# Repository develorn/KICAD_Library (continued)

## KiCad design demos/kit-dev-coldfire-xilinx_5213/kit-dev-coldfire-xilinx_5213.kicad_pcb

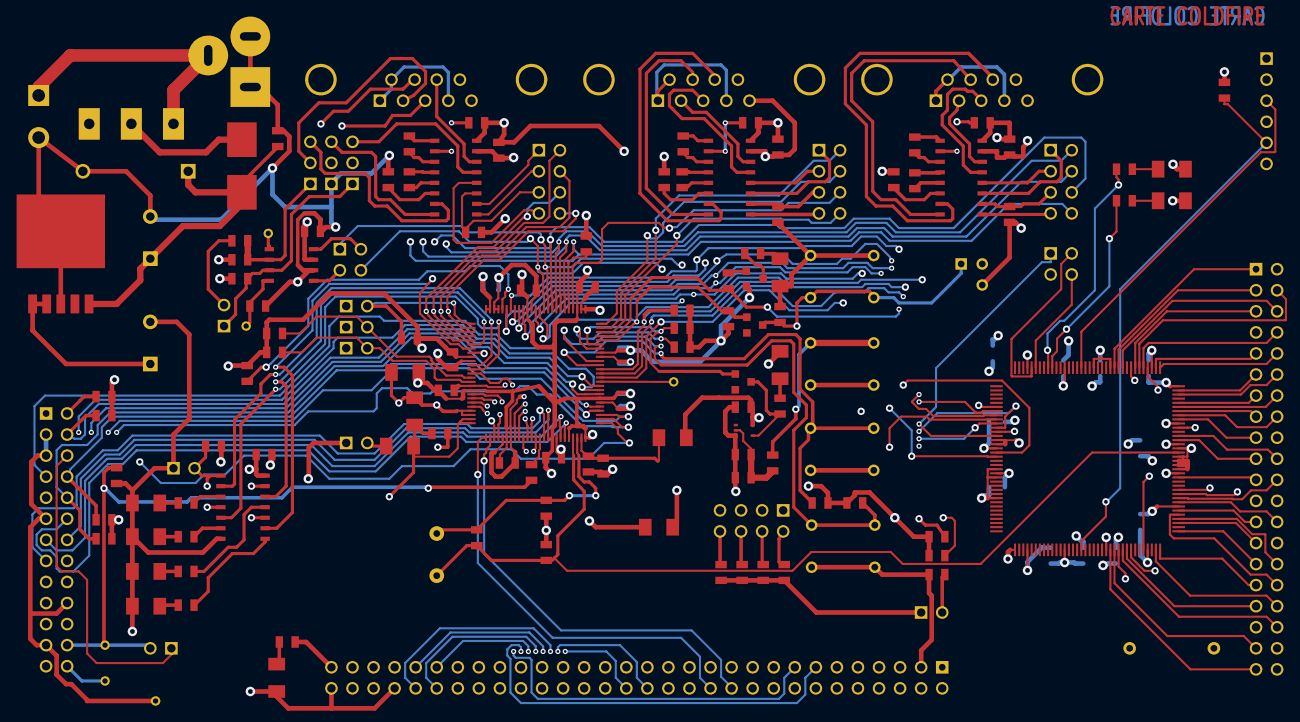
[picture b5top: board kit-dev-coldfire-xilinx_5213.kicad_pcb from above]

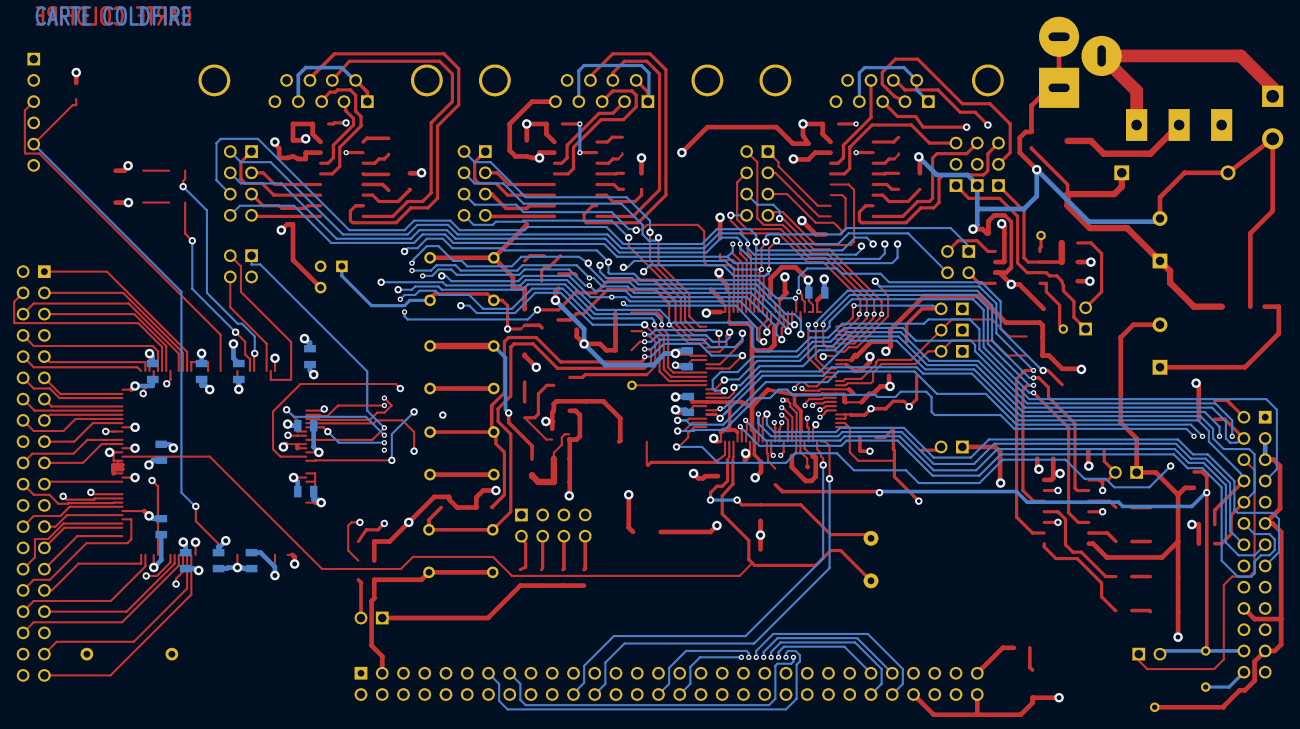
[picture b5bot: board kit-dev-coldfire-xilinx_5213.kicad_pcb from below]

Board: 4 copper layers, 162 parts (14 on the bottom side), 209 nets.

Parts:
ABRT_SW1: SW_PUSH; SW_PUSH_SMALL
ALLPST1: CONN_1; PINTST
BDM_EN1: JUMPER; PIN_ARRAY_2X1
BDM_PORT1: CONN_13X2; pin_array_13x2
C1, C2: 10pF; SM0805
C3, C20: 1nF; SM0805
C4, C5, C6, C7, C8, C9, C10, C11, C12, C14, C15, C18, C21, C22, C23, C24, C25, C26, C27, C28, C30, C31, C32, C33, C34, C35, C36, C41, C43, C44, C45, C46, C51, C52, C53, C54, C55, C56, C57, C58, C59, C60, C61: 100nF; SM0805
C16: 10uF; SM1206POL
C17: 100uF; SM1206POL
C38: 10uF; C2V8
C40: 220uF; C2V8
CAN_EN1: CONN_2X2; PIN_ARRAY_2X2
CAN_TERM1: JUMPER; PIN_ARRAY_2X1
CLK0, CLK1: JUMPER; PIN_ARRAY_2X1
CLKOUT1: CONN_1; PINTST
COM_SEL1, COM_SEL2, COM_SEL3: CONN_3; PIN_ARRAY_3X1
CT1: JUMPER; PIN_ARRAY_2X1
D1, D3: BAT54; ST23AK#1
D7: 1N4004; D5
D8, D9: LED; SM1206POL
F1: FUSE; FSUPCMS
FB1: BEAD; SM1206
GND1: CONN_1; PINTST
J1: JACK_2P; JACK_ALIM
L1, L2: 10uH; SM1206
LED1, LED2, LED3, LED4, LED5: LED; SM1206POL
LEDABRT1: RED; SM1206POL
LED_EN1: JUMPER; PIN_ARRAY_2X1
LV1: DS1818; TO92-INVERT
MCU_PORT1: CONN_30X2; PIN_ARRAY_30X2
P1: CONN_6; PIN_ARRAY-6X1
P3: CONN_2X2; PIN_ARRAY_2X2
P4: CONN_20X2; PIN_ARRAY_20X2
PULUPEN1: CONN_4X2; pin_array_4x2
Q1: 3906; SOT23EBC
R1: 1M; SM0805
R2, R15, R16, R17, R18, R19, R20, R21, R25, R45, R47, R48, R49, R50: 4,7K; SM0805
R4, R5, R6, R8, R10, R11, R13, R23, R26, R30, R34, R35: 10K; SM0805
R7, R36, R62, R63: 1K; SM0805
R9: 0; SM0805
R12: 20K; SM0805
R14, R22, R28, R31, R32, R33, R53: 270; SM0805
R38: 62; SM0805
R46: 22; SM0805
R57: 4K7; SM0805
R64: 3,3; R4
RCAN1, RCAN2: R; SM0805
RED1: LED_RESET1; SM1206POL
RS1: CONN_1; PINTST
RST_SW1: SW_PUSH; SW_PUSH_SMALL
SW1, SW2: SW_PUSH; SW_PUSH_SMALL
SW_ONOFF1: SWITCH_INV; SW_SPDT
TA-1: CONN_1; PINTST
TB1: CONN_2; bornier2
U1: MCF5213-LQFP100; VQFP100
U2: 74AHC1G14; SOT353
U3, U5, U8: MAX202; SO16E
U4: 74HC125; SO14E
U7: PCA82C251; SO8E
U9: XCR3256-TQ144; TQFP144
UARTCAN0, UARTCAN1, UARTCAN2: DB9; DB9FC
UART_EN0, UART_EN1, UART_EN2: CONN_4X2; pin_array_4x2
VDDA1: JUMPER; PIN_ARRAY_2X1
VR1: LT1129_QPACK; DPAK5
VREF1: CONN_1; PINTST
VX_EN1: JUMPER; PIN_ARRAY_2X1
Y1: 8MHz; HC-18UH

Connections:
+3.3V: ABRT_SW1.2, BDM_PORT1.9, BDM_PORT1.25, C4.1, C5.1, C6.1, C7.1, C8.1, C9.1, C10.1, C11.1, C12.1, C14.2, C17.1, C22.1, C23.1, C26.1, C28.1, C30.1, C34.1, C35.1, C40.1, C46.1, C51.1, C52.1, C53.1, C54.1, C55.1, C56.1, C57.1, C58.1, C59.1, C60.1, C61.1, L2.1, LEDABRT1.1, LV1.2, MCU_PORT1.59, P1.1, Q1.1, R2.1, R4.2, R5.2, R6.2, R8.2, R10.2, R11.2, R13.2, R15.1, R16.1, R17.1, R18.1, R19.1, R20.1, R25.1, R34.1, R45.2, R47.1, R48.1, R49.1, R50.1, R53.2, R57.1, R64.1, RCAN1.1, U1.1, U1.2, U1.14, U1.22, U1.23, U1.34, U1.41, U1.55, U1.57, U1.68, U1.81, U1.93, U2.5, U3.16, U4.14, U5.16, U7.3, U8.16, U9.24, U9.50, U9.51, U9.58, U9.73, U9.76, U9.95, U9.115, U9.123, U9.130, U9.144, VDDA1.1, VR1.1, VR1.2, VX_EN1.1
/ALLPST: ALLPST1.1, U1.86
/AN2: MCU_PORT1.14, U1.45
/AN3: MCU_PORT1.16, U1.46
/AN4: MCU_PORT1.18, U1.54
/AN6: MCU_PORT1.22, U1.52
/BKPT-: BDM_PORT1.2, R17.2, U1.76
/CANTX: CAN_EN1.1, MCU_PORT1.26, PULUPEN1.5, U1.10
/CLKIN/EXTAL: C1.1, R1.2, U1.73, Y1.1
/CLKMOD0: CLK0.2, R25.2, U1.40
/CLKMOD1: CLK1.2, R2.2, U1.39
/DDAT0: BDM_PORT1.19, U1.77
/DDAT1: BDM_PORT1.18, U1.78
/DDAT2: BDM_PORT1.17, U1.83
/DDAT3: BDM_PORT1.16, U1.84
/DSCLK: BDM_PORT1.4, R18.2, U1.85
/DSI: BDM_PORT1.8, R19.2, U1.79
/DSO: BDM_PORT1.10, R20.2, U1.80
/DSPI_DOUT: MCU_PORT1.17, U1.17, U9.47
/DTIN1: MCU_PORT1.36, U1.37, U4.5
/GPT1: MCU_PORT1.50, U1.59
/GPT3: MCU_PORT1.52, U1.62
/IRQ-5: MCU_PORT1.35, R10.1, SW2.1, U1.91
/IRQ-6: MCU_PORT1.37, R11.1, U1.94
/IRQ-7: D1.1, MCU_PORT1.39, R13.1, U1.95
/JTAG_EN: BDM_EN1.2, R16.2, U1.26
/PST0: BDM_PORT1.15, U1.65
/PST1: BDM_PORT1.14, U1.66
/PST2: BDM_PORT1.13, U1.69
/PST3: BDM_PORT1.12, U1.70
/PWM1: MCU_PORT1.13, U1.38
/PWM3: MCU_PORT1.15, U1.33
/QSPI_CS3: MCU_PORT1.29, U1.12
/QSPI_DIN: MCU_PORT1.19, U1.16, U9.46
/RCON-: MCU_PORT1.53, R45.1, U1.21
/RSTI-: BDM_PORT1.7, D3.1, MCU_PORT1.6, R15.2, U1.96
/RSTO-: MCU_PORT1.4, R21.1, U1.97
/TCLK: BDM_PORT1.24, CLKOUT1.1, CT1.2, R26.1, R46.2
/UCTS0: MCU_PORT1.44, U1.6, UART_EN0.8
/URTS1: MCU_PORT1.9, P3.3, U1.4, U9.53, UART_EN1.6
/URXD0: MCU_PORT1.43, U1.7, UART_EN0.4
/UTXD1: MCU_PORT1.5, U1.99, UART_EN1.2
/UTXD2: MCU_PORT1.45, U1.29, UART_EN2.2
/VCCA: C16.1, C18.1, L1.2, MCU_PORT1.55, MCU_PORT1.57, U1.49, U1.50
/VDDPLL: C20.1, C21.1, L2.2, U1.74
/inout_user/AN0: MCU_PORT1.10, U1.43
/inout_user/AN1: MCU_PORT1.12, U1.44
/inout_user/AN5: MCU_PORT1.20, U1.53
/inout_user/AN7: MCU_PORT1.24, U1.51
/inout_user/CANRX: CAN_EN1.4, MCU_PORT1.28, PULUPEN1.7, U1.11
/inout_user/CAN_H: CAN_TERM1.1, COM_SEL1.1, RCAN2.2, U7.7
/inout_user/CAN_L: COM_SEL3.1, R38.1, RCAN1.2, U7.6
/inout_user/CTS0: U3.8, UARTCAN0.7
/inout_user/CTS1: U5.8, UARTCAN1.7
/inout_user/CTS2/CANH: COM_SEL1.2, UARTCAN2.7
/inout_user/DTIN0: MCU_PORT1.34, U1.36, U4.2
/inout_user/DTIN2: MCU_PORT1.38, U1.31, U4.12
/inout_user/DTIN3: MCU_PORT1.40, U1.32, U4.9
/inout_user/GPT0: MCU_PORT1.49, U1.58
/inout_user/GPT2: MCU_PORT1.51, U1.61
/inout_user/IRQ-4: MCU_PORT1.33, R8.1, SW1.1, U1.90
/inout_user/PWM5: MCU_PORT1.30, U1.60
/inout_user/PWM7: MCU_PORT1.32, U1.63
/inout_user/QSPI_CS0: MCU_PORT1.23, PULUPEN1.3, U1.20
/inout_user/QSPI_CS1: MCU_PORT1.25, U1.19, U9.54
/inout_user/RTS0: U3.7, UARTCAN0.8
/inout_user/RTS1: U5.7, UARTCAN1.8
/inout_user/RTS2: U8.14, UARTCAN2.8
/inout_user/RXD0: U3.13, UARTCAN0.3
/inout_user/RXD1: U5.13, UARTCAN1.3
/inout_user/RXD2: COM_SEL2.2, UARTCAN2.3
/inout_user/RxD_CAN: CAN_EN1.2, U7.4
/inout_user/TXD0: U3.14, UARTCAN0.2
/inout_user/TXD1: U5.14, UARTCAN1.2
/inout_user/TXD2/CANL: COM_SEL3.2, UARTCAN2.2
/inout_user/TxD_CAN: CAN_EN1.3, U7.1
/inout_user/UCTS2: MCU_PORT1.48, U1.27, UART_EN2.8
/inout_user/URTS0: MCU_PORT1.42, U1.9, UART_EN0.6
/inout_user/URTS2: MCU_PORT1.46, U1.30, UART_EN2.6
/inout_user/URXD1: MCU_PORT1.7, U1.100, UART_EN1.4
/inout_user/URXD2: MCU_PORT1.47, U1.28, UART_EN2.4
/inout_user/UTXD0: MCU_PORT1.41, U1.8, UART_EN0.2
/inout_user/VRL: C16.2, C18.2, FB1.2, MCU_PORT1.56, MCU_PORT1.58, U1.47, U1.48
/xilinx/+3,3V_OUT: P4.38, R64.2
/xilinx/GLCK2: C2.1, R1.1, U1.72, U9.128, Y1.2
/xilinx/LED_TEST1: R62.1, U9.28
/xilinx/LED_TEST2: R63.1, U9.27
/xilinx/QSPI_CS2: MCU_PORT1.27, U1.13, U9.45
/xilinx/QSPI_SCLK: MCU_PORT1.21, PULUPEN1.1, U1.18, U9.48
/xilinx/TCK: P1.5, R57.2, U9.89
/xilinx/TDI: P1.4, U9.4
/xilinx/TDO: P1.6, U9.104
/xilinx/TMS: P1.3, U9.20
/xilinx/UCTS1-: MCU_PORT1.11, P3.1, U1.98, U9.49, UART_EN1.8
/xilinx/XIL_D0: P4.1, U9.12
/xilinx/XIL_D1: P4.3, U9.11
/xilinx/XIL_D2: P4.5, U9.7
/xilinx/XIL_D3: P4.7, U9.8
/xilinx/XIL_D4: P4.9, U9.2
/xilinx/XIL_D5: P4.11, U9.143
/xilinx/XIL_D6: P4.13, U9.140
/xilinx/XIL_D7: P4.15, U9.138
/xilinx/XIL_D8: P4.17, U9.136
/xilinx/XIL_D9: P4.19, U9.131
/xilinx/XIL_D10: P4.21, U9.122
/xilinx/XIL_D11: P4.23, U9.119
/xilinx/XIL_D12: P4.25, U9.114
/xilinx/XIL_D13: P4.27, U9.111
/xilinx/XIL_D14: P4.29, U9.109
/xilinx/XIL_D15: P4.31, U9.108
/xilinx/XIL_D16: P4.33, U9.100
/xilinx/XIL_D17: P4.35, U9.101
/xilinx/XIL_D18: P4.37, U9.97
/xilinx/XIL_D19: P4.39, U9.96
/xilinx/XIL_D20: P4.4, U9.6
/xilinx/XIL_D21: P4.6, U9.10
/xilinx/XIL_D22: P4.8, U9.5
/xilinx/XIL_D23: P4.10, U9.1
/xilinx/XIL_D24: P4.12, U9.142
/xilinx/XIL_D25: P4.14, U9.139
/xilinx/XIL_D26: P4.16, U9.137
/xilinx/XIL_D27: P4.18, U9.134
/xilinx/XIL_D28: P4.20, U9.132
/xilinx/XIL_D29: P4.22, U9.117
/xilinx/XIL_D30: P4.24, U9.118
/xilinx/XIL_D31: P4.26, U9.116
/xilinx/XIL_D32: P4.28, U9.98
/xilinx/XIL_D33: P4.30, U9.112
/xilinx/XIL_D34: P4.32, U9.113
/xilinx/XIL_D35: P4.34, U9.107
/xilinx/XIL_D36: P4.36, U9.99
/xilinx/XIL_INIT: MCU_PORT1.31, R6.1, U1.89, U9.44
/xilinx/XIL_IRQ1: MCU_PORT1.2, R4.1, U1.87, U9.42
/xilinx/XIL_IRQ2: MCU_PORT1.8, R5.1, U1.88, U9.43
GND: BDM_EN1.1, BDM_PORT1.3, BDM_PORT1.5, BDM_PORT1.11, BDM_PORT1.20, BDM_PORT1.23, C1.2, C2.2, C3.2, C4.2, C5.2, C6.2, C7.2, C8.2, C9.2, C10.2, C11.2, C12.2, C14.1, C15.2, C17.2, C20.2, C21.2, C22.2, C26.2, C27.2, C28.2, C33.2, C34.2, C38.2, C40.2, C41.2, C43.1, C45.2, C46.2, C51.2, C52.2, C53.2, C54.2, C55.2, C56.2, C57.2, C58.2, C59.2, C60.2, C61.2, CLK0.1, CLK1.1, COM_SEL2.1, D7.1, D8.2, D9.2, FB1.1, GND1.1, J1.1, J1.2, LED1.2, LED2.2, LED3.2, LED4.2, LED5.2, LED_EN1.1, LV1.3, MCU_PORT1.3, MCU_PORT1.54, MCU_PORT1.60, P1.2, P4.2, P4.40, R9.2, R12.2, R23.1, R26.2, R30.1, R35.1, R36.2, RCAN2.1, RED1.2, RST_SW1.2, SW1.2, SW2.2, TB1.2, U1.3, U1.15, U1.24, U1.25, U1.35, U1.42, U1.56, U1.67, U1.71, U1.75, U1.82, U1.92, U2.3, U3.15, U4.7, U5.15, U7.2, U8.15, U9.3, U9.13, U9.17, U9.33, U9.52, U9.57, U9.59, U9.64, U9.85, U9.105, U9.124, U9.125, U9.126, U9.127, U9.129, U9.135, UARTCAN0.5, UARTCAN1.5, UARTCAN2.5, VR1.3
unnamed: R22.2, RED1.1
unnamed: L1.1, VDDA1.2
unnamed: Q1.3, R22.1
unnamed: Q1.2, R21.2
unnamed: R46.1, U1.64
unnamed: BDM_PORT1.6, CT1.1
unnamed: LEDABRT1.2, R14.1
unnamed: ABRT_SW1.1, R7.1
unnamed: BDM_PORT1.26, TA-1.1
unnamed: D1.2, R14.2, U2.4
unnamed: C15.1, R7.2, R12.1, U2.2
unnamed: R9.1, U1.5
unnamed: C3.1, D3.2, LV1.1, RST_SW1.1
unnamed: C27.1, U3.6
unnamed: C32.2, U5.5
unnamed: C31.1, U5.1
unnamed: C31.2, U5.3
unnamed: C30.2, U5.2
unnamed: U5.9, UART_EN1.7
unnamed: R35.2, U5.10, UART_EN1.5
unnamed: U5.12, UART_EN1.3
unnamed: U5.11, UART_EN1.1
unnamed: UARTCAN1.1, UARTCAN1.4, UARTCAN1.6
unnamed: C25.1, U3.4
unnamed: C25.2, U3.5
unnamed: C24.1, U3.1
unnamed: C24.2, U3.3
unnamed: C23.2, U3.2
unnamed: U3.9, UART_EN0.7
unnamed: U3.12, UART_EN0.3
unnamed: U3.11, UART_EN0.1
unnamed: UARTCAN0.1, UARTCAN0.4, UARTCAN0.6
unnamed: C45.1, U8.6
unnamed: COM_SEL1.3, U8.13
unnamed: COM_SEL2.3, U8.8
unnamed: U8.9, UART_EN2.3
unnamed: C36.2, U8.5
unnamed: C36.1, U8.4
unnamed: C44.2, U8.3
unnamed: C44.1, U8.1
unnamed: C33.1, U5.6
unnamed: C32.1, U5.4
unnamed: U8.12, UART_EN2.7
unnamed: U8.10, UART_EN2.1
unnamed: UARTCAN2.1, UARTCAN2.4, UARTCAN2.6
unnamed: C35.2, U8.2
unnamed: R32.2, U4.11
unnamed: LED2.1, R31.1
unnamed: R31.2, U4.6
unnamed: LED1.1, R28.1
unnamed: R28.2, U4.3
unnamed: R33.2, U4.8
unnamed: LED_EN1.2, R34.2, U4.1, U4.4, U4.10, U4.13
unnamed: LED4.1, R33.1
unnamed: LED3.1, R32.1
unnamed: C43.2, MCU_PORT1.1, VX_EN1.2
unnamed: PULUPEN1.8, R47.2
unnamed: PULUPEN1.4, R49.2
unnamed: R23.2, U8.11, UART_EN2.5
unnamed: R36.1, RS1.1, U7.8
unnamed: J1.3, SW_ONOFF1.3, TB1.1
unnamed: F1.1, SW_ONOFF1.2
unnamed: C38.1, C41.1, D7.2, F1.2, VR1.5
unnamed: LED5.1, R53.1
unnamed: U7.5, VREF1.1
unnamed: PULUPEN1.6, R48.2
unnamed: PULUPEN1.2, R50.2
unnamed: R30.2, U3.10, UART_EN0.5
unnamed: COM_SEL3.3, U8.7
unnamed: CAN_TERM1.2, R38.2
unnamed: P3.4, U9.31
unnamed: D8.1, R62.2
unnamed: D9.1, R63.2
unnamed: P3.2, U9.32

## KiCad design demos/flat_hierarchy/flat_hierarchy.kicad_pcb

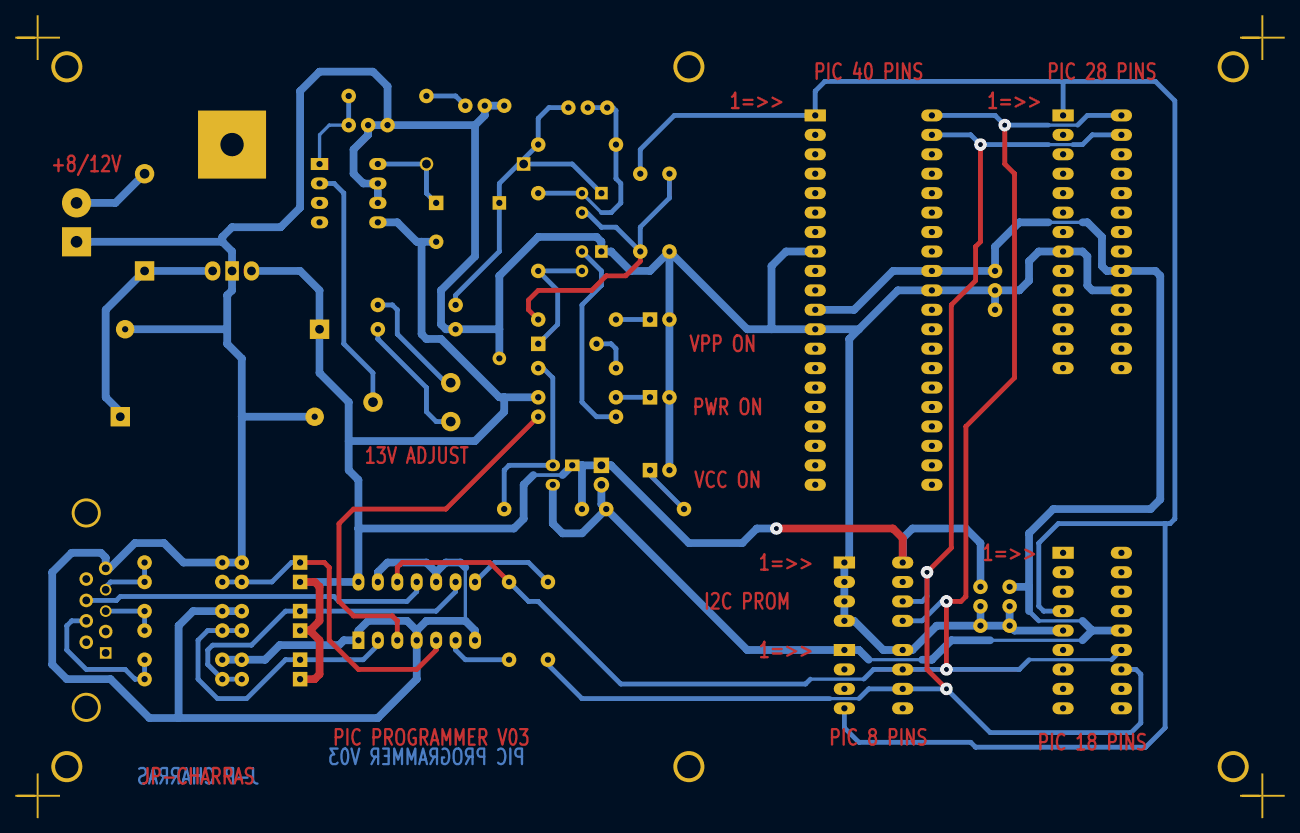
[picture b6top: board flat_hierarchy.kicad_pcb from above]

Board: 2 copper layers, 68 parts (0 on the bottom side), 34 nets.

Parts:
1PIN, 1PIN#2, 1PIN#3, 1PIN#4, 1PIN#5, 1PIN#6: P***; 1pin
C1: 100uF; CP10
C2: 220uF; CP10
C3: 22uF/25V; CP8
C4: 0; C1-1
C5: 10nF; C1-1
C6, C7, C8: 100nF; C1-1
C9: 22OnF; C1-1
D1: 1N4004; D5
D2, D3, D4, D5, D6, D7, D11: BAT43; D3
D8: RED-LED; LEDV
D9: GREEN-LED; LEDV
D10: SCHOTTKY; D5
D12: YELLOW-LED; LEDV
J1: DB9-FEMAL; DB9FC
JP1: JUMPER; PIN_ARRAY_2X1
L1: 22uH; INDUCTOR_V
MIRE: *; MIRE
MIRE#2, MIRE#3, MIRE#4: *; MIRE
P1: CONN_2; bornier2
P2: SUPP28; 28DIP-ELL300
P3: SUPP40; 40DIP-ELL600
Q1: BC237; TO92
Q2, Q3: BC307; TO92
R1, R2, R3, R4, R5, R6, R7: 10K; R4
R8: 1K; R4
R9, R19, R20: 2.2K; R4
R10: 5,1K; R4
R11, R17: 22K; R4
R12, R13, R14, R21: 470; R4
R15: 6.2K; R4
R16: 62K; R4
R18: 220; R4
RV1: 1K; RV2X4
U1: 24Cxx; 8DIP-ELL300
U2: 74HC125; 14DIP-ELL300
U3: 7805; LM78XX
U4: LT1373; 8DIP-ELL300
U5: PIC_18_PINS; 18DIP-ELL300
U6: PIC_8_PINS; 8DIP-ELL300

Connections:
CLOCK-RB6_1: P2.27, P3.39, R13.2, U1.6, U5.12, U6.6
CTS_1: J1.8, U2.11
DATA-RB7_2: P2.28, P3.40, R12.2, U1.5, U2.12, U5.13, U6.7
GND: C1.2, C2.2, C3.2, C4.2, C5.2, C6.2, C7.2, C8.2, D3.1, D5.1, D7.1, D8.2, D9.2, D12.2, J1.5, P1.1, P2.8, P2.19, P3.8, P3.12, P3.31, Q1.1, R2.2, R4.2, R6.2, R15.2, R17.2, U1.1, U1.2, U1.3, U1.4, U2.1, U2.4, U2.7, U2.10, U2.13, U3.GND, U4.6, U4.7, U5.5, U6.8
unnamed: Q2.3, R9.1, R17.1, R18.1
unnamed: Q3.2, R19.2, R20.2
unnamed: D2.1, D3.2, R1.2, U2.2
unnamed: D4.1, D5.2, R3.2, U2.5
unnamed: D6.1, D7.2, R5.2, U2.9
unnamed: R12.1, U2.6
unnamed: R8.1, U2.3
unnamed: R13.1, U2.8
unnamed: D8.1, R9.2
unnamed: D11.2, Q1.3, R11.1
unnamed: Q1.2, R8.2
unnamed: D1.1, P1.2
unnamed: C2.1, D1.2, U3.VI
unnamed: D9.1, R14.2
unnamed: D10.1, L1.1, U4.8
unnamed: C4.1, R10.1, U4.1
unnamed: C5.1, R10.2
unnamed: R16.1, RV1.3
unnamed: R15.1, RV1.1
unnamed: RV1.2, U4.2
unnamed: D12.1, R21.1
unnamed: D11.1, R19.1
unnamed: C9.2, Q2.2, R7.2, R11.2
PC-CLOCK-OUT_1: J1.7, R5.1, R6.1
PC-DATA-OUT_1: J1.4, R3.1, R4.1
VCC: C1.1, C6.1, D2.2, D4.2, D6.2, JP1.1, L1.2, Q3.1, R14.1, R20.1, U1.8, U2.14, U3.VO, U4.5
VCC_PIC_2: C7.1, C8.1, JP1.2, P2.20, P3.11, P3.32, Q3.3, R21.2, U5.14, U6.1
VPP: C3.1, C9.1, D10.2, Q2.1, R7.1, R16.2
VPP-MCLR_2: P2.1, P3.1, R18.2, U5.4, U6.4
VPP_ON_1: J1.3, R1.1, R2.1

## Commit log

2014-10-09 Kicad library
2014-10-26 Switch
2014-11-04 Add H bridge tb6612
2014-11-08 microswitch footprint, oscilator and pin array footprint
